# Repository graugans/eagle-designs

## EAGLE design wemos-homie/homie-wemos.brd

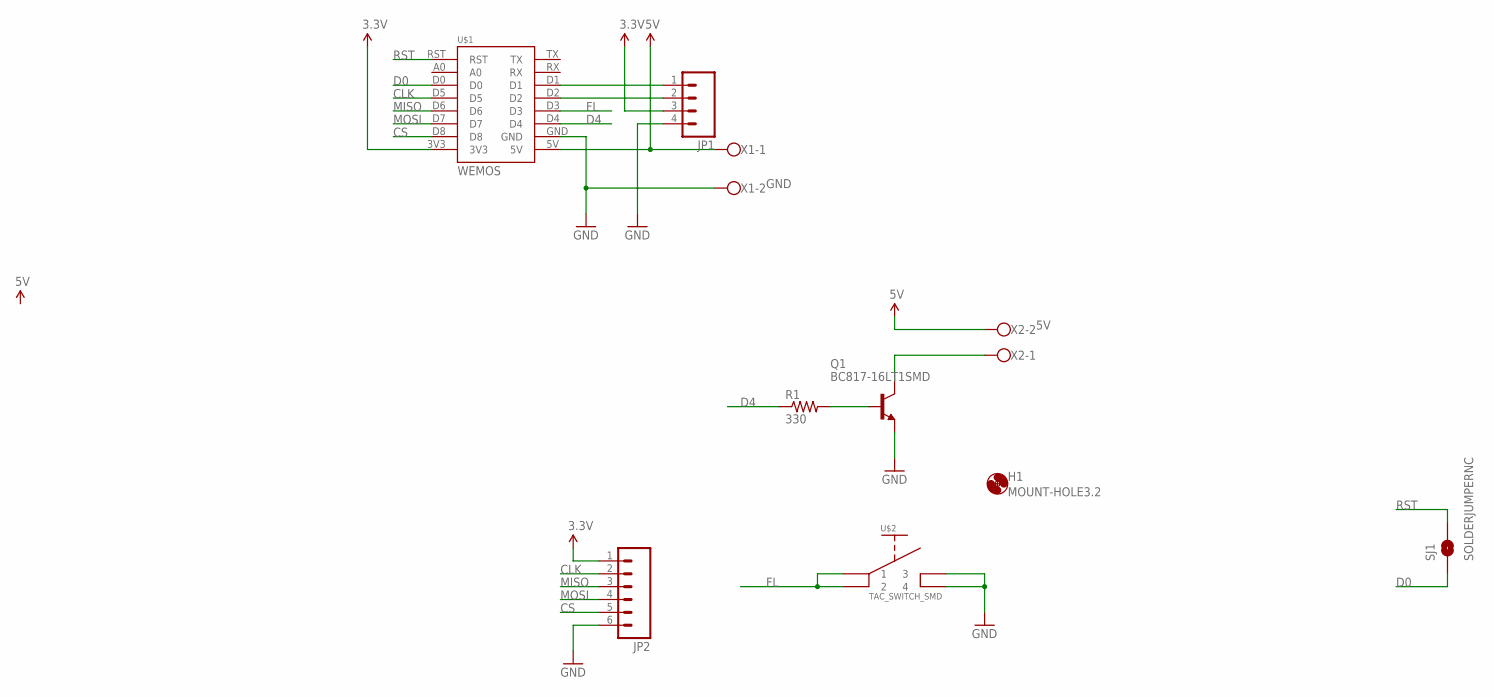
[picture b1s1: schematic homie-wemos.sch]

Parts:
H1: MOUNT-HOLE3.2; 3,2
JP1: M04LOCK_LONGPADS; 1X04_LOCK_LONGPADS
JP2: M06LOCK_LONGPADS; 1X06_LOCK_LONGPADS
Q1: BC817-16LT1SMD; SOT23-BEC
R1: 330; 0603-RES
SJ1: SOLDERJUMPERNC; SJ_2S
U$1: WEMOS
U$2: TS-017A; TS-017ASMD
X1, X2: W237-102

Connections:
3.3V: JP1.3, JP2.1, U$1.3V3
5V: U$1.5V, X1.1, X2.2
CLK: JP2.2, U$1.D5
CS: JP2.5, U$1.D8
D0: SJ1.1, U$1.D0
D4: R1.1, U$1.D4
FL: U$1.D3, U$2.P$1 (1), U$2.P$2 (2)
GND: JP1.4, JP2.6, Q1.E, U$1.GND, U$2.P$3 (3), U$2.P$4 (4), X1.2
MISO: JP2.3, U$1.D6
MOSI: JP2.4, U$1.D7
unnamed: JP1.1, U$1.D1
unnamed: JP1.2, U$1.D2
unnamed: Q1.C, X2.1
unnamed: Q1.B, R1.2
RST: SJ1.2, U$1.RST

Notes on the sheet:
GND

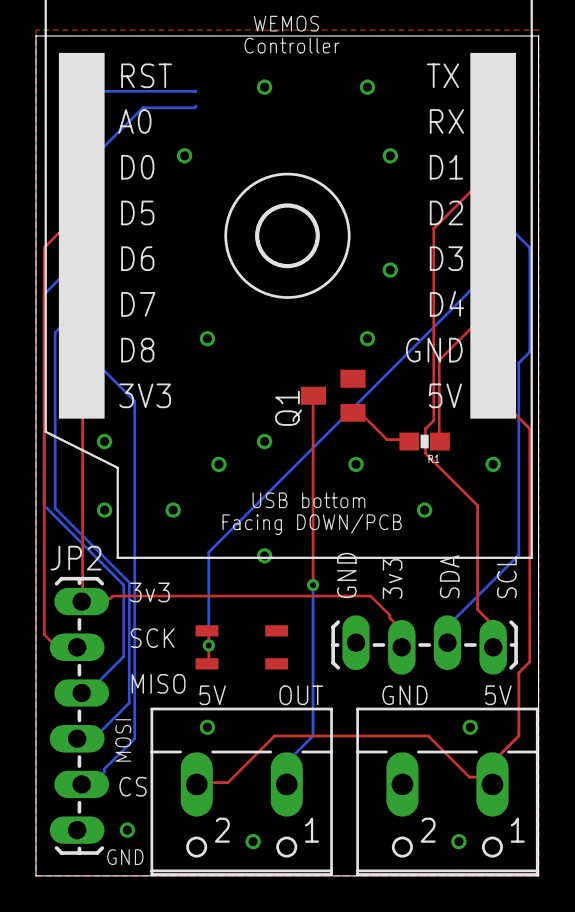
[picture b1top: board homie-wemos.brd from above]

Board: 2 copper layers, 27.9 x 46.7 mm, 10 parts (1 on the bottom side), 15 nets.

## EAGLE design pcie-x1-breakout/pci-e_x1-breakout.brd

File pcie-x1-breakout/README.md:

# This is a breakout board for a PCIe X1 36P female connector

If you are interested in such a board you can order your own board at [OSHPark](https://oshpark.com/shared_projects/meplccNm)

![Top view of the board][top_image]
![Bottom view of the board][bottom_image]

The JP3 is intended to connect the top and bottom copper planes with ground (GND) this is to improve signal integrity.

[bottom_image]: https://644db4de3505c40a0444-327723bce298e3ff5813fb42baeefbaa.ssl.cf1.rackcdn.com/uploads/project/bottom_image/meplccNm/i.png "Botton Layer view" 
[top_image]: https://644db4de3505c40a0444-327723bce298e3ff5813fb42baeefbaa.ssl.cf1.rackcdn.com/uploads/project/top_image/meplccNm/i.png "Top Layer view"

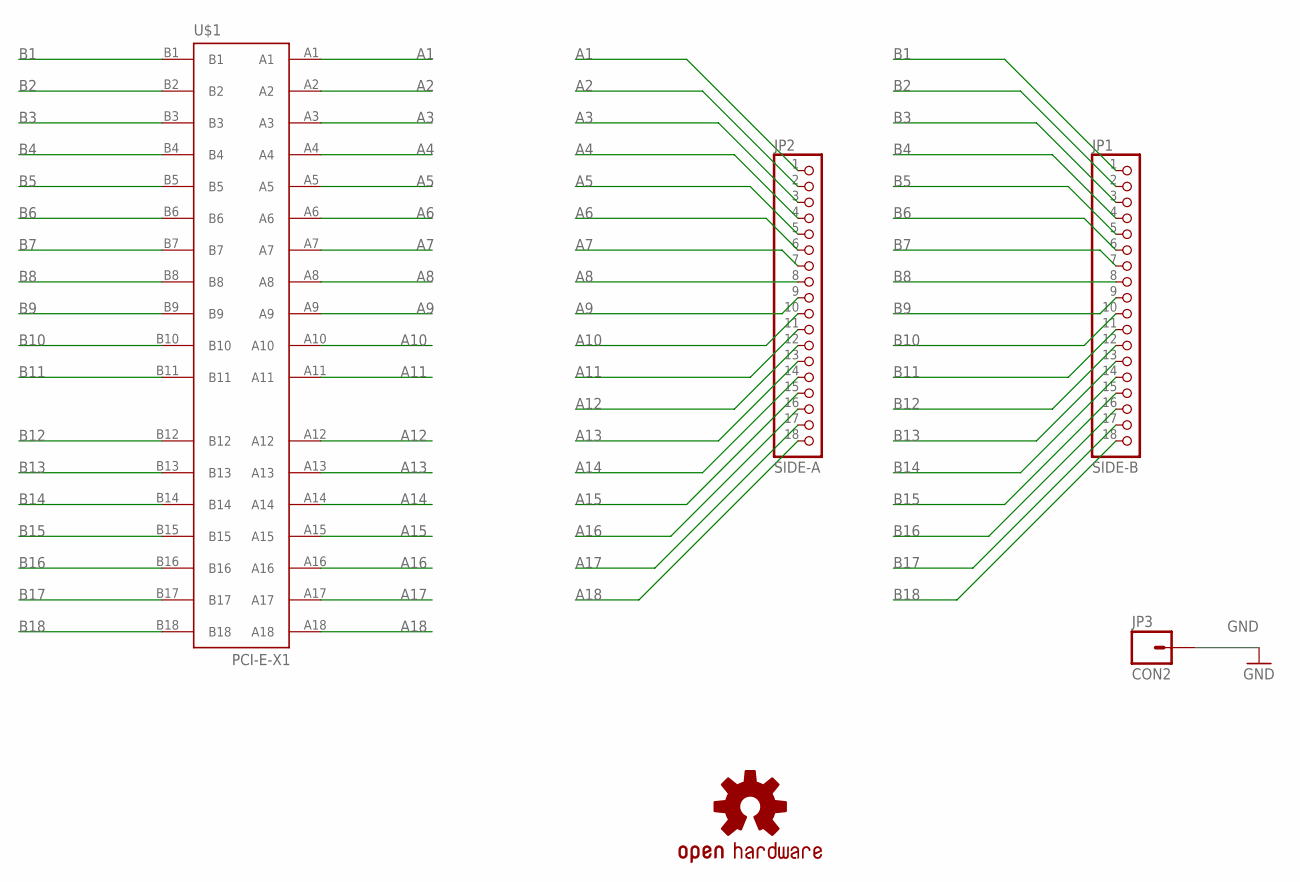
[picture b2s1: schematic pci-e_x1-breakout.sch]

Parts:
JP1: SIDE-B; 1X18
JP2: SIDE-A; 1X18
JP3: CON2; 1X01
LOGO1: OSHW-LOGOS; OSHW-LOGO-S
U$1: PCI-E-X1

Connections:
A1: JP2.1, U$1.A1
A2: JP2.2, U$1.A2
A3: JP2.3, U$1.A3
A4: JP2.4, U$1.A4
A5: JP2.5, U$1.A5
A6: JP2.6, U$1.A6
A7: JP2.7, U$1.A7
A8: JP2.8, U$1.A8
A9: JP2.9, U$1.A9
A10: JP2.10, U$1.A10
A11: JP2.11, U$1.A11
A12: JP2.12, U$1.A12
A13: JP2.13, U$1.A13
A14: JP2.14, U$1.A14
A15: JP2.15, U$1.A15
A16: JP2.16, U$1.A16
A17: JP2.17, U$1.A17
A18: JP2.18, U$1.A18
B1: JP1.1, U$1.B1
B2: JP1.2, U$1.B2
B3: JP1.3, U$1.B3
B4: JP1.4, U$1.B4
B5: JP1.5, U$1.B5
B6: JP1.6, U$1.B6
B7: JP1.7, U$1.B7
B8: JP1.8, U$1.B8
B9: JP1.9, U$1.B9
B10: JP1.10, U$1.B10
B11: JP1.11, U$1.B11
B12: JP1.12, U$1.B12
B13: JP1.13, U$1.B13
B14: JP1.14, U$1.B14
B15: JP1.15, U$1.B15
B16: JP1.16, U$1.B16
B17: JP1.17, U$1.B17
B18: JP1.18, U$1.B18

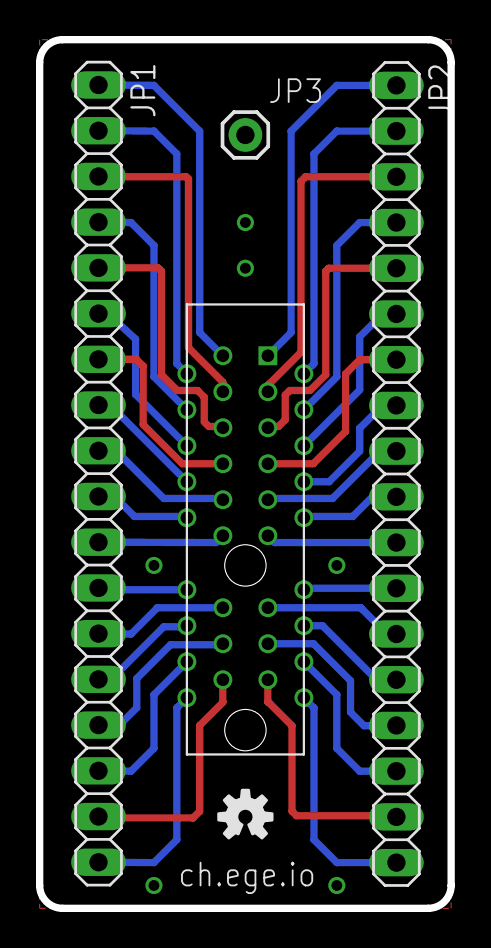
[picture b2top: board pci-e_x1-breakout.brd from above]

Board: 2 copper layers, 22.9 x 48.3 mm, 5 parts (0 on the bottom side), 36 nets.

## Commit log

2015-07-26 Added GNU AFFERO GENERAL PUBLIC LICENSE
2015-07-26 PCIe X1 36P breakout board
2015-07-26 Added gerber and autoroute files to ignore list
2015-07-26 Added a read me file to the PCIe breakout
2015-07-26 Fixed typo and added images
2015-07-26 Hint about JP3
2015-07-26 PDF of schematic view added
2016-07-07 Added a baseboard for the Wemos D1 mini
    This is a baseboard prototype for the Homie-ESP8266 framework. It provides an push button to enter the set-up mode and breaks out the I2C and SPI bus. To switch higher loads it provides an transistor.

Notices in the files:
parts and their libraries:
SparkFun-Aesthetics: Licensing: Creative Commons ShareAlike 4.0 International - https://creativecommons.org/licenses/by-sa/4.0
